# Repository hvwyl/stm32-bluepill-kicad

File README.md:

# stm32-bluepill-kicad
STM32 BluePill redesigned by KiCad

## Schematic

## PCB Layout

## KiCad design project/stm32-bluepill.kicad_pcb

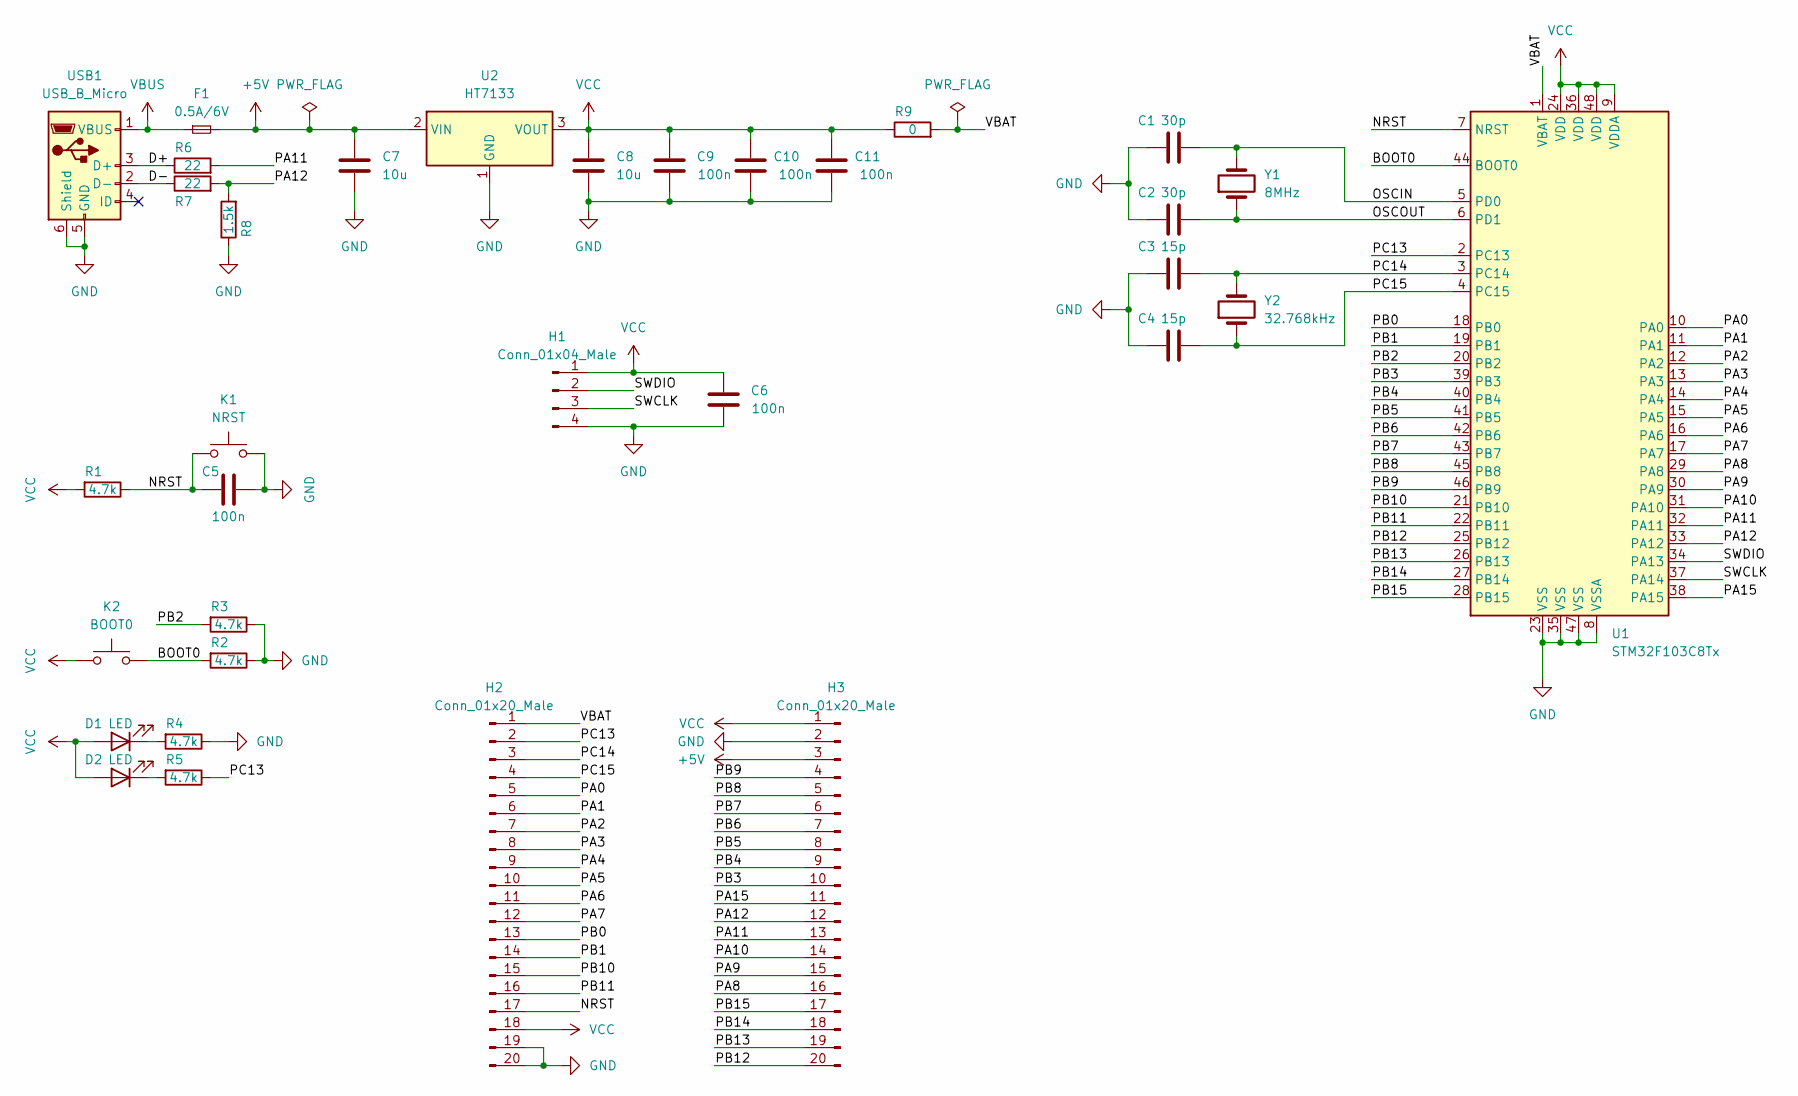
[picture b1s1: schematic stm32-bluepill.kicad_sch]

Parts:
C1, C2: 30p; C_0603_1608Metric
C3, C4: 15p; C_0603_1608Metric
C5, C6, C9, C10, C11: 100n; C_0603_1608Metric
C7, C8: 10u; C_0805_2012Metric
D1, D2: LED; LED_0805_2012Metric
F1: 0.5A/6V; Fuse_0805_2012Metric
H1: Conn_01x04_Male; PinHeader_1x04_P2.54mm_Vertical
H2, H3: Conn_01x20_Male; PinHeader_1x20_P2.54mm_Vertical
K1: NRST; SW_SPST_CK_RS282G05A3
K2: BOOT0; SW_SPST_CK_RS282G05A3
R1, R2, R3, R4, R5: 4.7k; R_0603_1608Metric
R6, R7: 22; R_0603_1608Metric
R8: 1.5k; R_0603_1608Metric
R9: 0; R_0603_1608Metric
U1: STM32F103C8Tx; LQFP-48_7x7mm_P0.5mm
U2: HT7133; SOT-89-3
USB1: USB_B_Micro; USB_Micro-B_Amphenol_10118194_Horizontal
Y1: 8MHz; Crystal_HC49-4H_Vertical
Y2: 32.768kHz; Crystal_DS26_D2.0mm_L6.0mm_Horizontal

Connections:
+5V: C7.1, F1.2, H3.3, U2.2 (VIN)
/BOOT0: K2.2, R2.2, U1.44 (BOOT0)
/D+: R6.1, USB1.3 (D+)
/D-: R7.1, USB1.2 (D-)
/NRST: C5.2, H2.17, K1.1, R1.1, U1.7 (NRST)
/OSCIN: C1.2, U1.5 (PD0), Y1.2
/OSCOUT: C2.2, U1.6 (PD1), Y1.1
/PA0: H2.5, U1.10 (PA0)
/PA1: H2.6, U1.11 (PA1)
/PA2: H2.7, U1.12 (PA2)
/PA3: H2.8, U1.13 (PA3)
/PA4: H2.9, U1.14 (PA4)
/PA5: H2.10, U1.15 (PA5)
/PA6: H2.11, U1.16 (PA6)
/PA7: H2.12, U1.17 (PA7)
/PA8: H3.16, U1.29 (PA8)
/PA9: H3.15, U1.30 (PA9)
/PA10: H3.14, U1.31 (PA10)
/PA11: H3.13, R6.2, U1.32 (PA11)
/PA12: H3.12, R7.2, R8.2, U1.33 (PA12)
/PA15: H3.11, U1.38 (PA15)
/PB0: H2.13, U1.18 (PB0)
/PB1: H2.14, U1.19 (PB1)
/PB2: R3.2, U1.20 (PB2)
/PB3: H3.10, U1.39 (PB3)
/PB4: H3.9, U1.40 (PB4)
/PB5: H3.8, U1.41 (PB5)
/PB6: H3.7, U1.42 (PB6)
/PB7: H3.6, U1.43 (PB7)
/PB8: H3.5, U1.45 (PB8)
/PB9: H3.4, U1.46 (PB9)
/PB10: H2.15, U1.21 (PB10)
/PB11: H2.16, U1.22 (PB11)
/PB12: H3.20, U1.25 (PB12)
/PB13: H3.19, U1.26 (PB13)
/PB14: H3.18, U1.27 (PB14)
/PB15: H3.17, U1.28 (PB15)
/PC13: H2.2, R5.1, U1.2 (PC13)
/PC14: C3.2, H2.3, U1.3 (PC14), Y2.2
/PC15: C4.2, H2.4, U1.4 (PC15), Y2.1
/SWCLK: H1.3, U1.37 (PA14)
/SWDIO: H1.2, U1.34 (PA13)
/VBAT: H2.1, R9.2, U1.1 (VBAT)
GND: C1.1, C2.1, C3.1, C4.1, C5.1, C6.1, C7.2, C8.2, C9.1, C10.1, C11.1, H1.4, H2.19, H2.20, H3.2, K1.2, R2.1, R3.1, R4.1, R8.1, U1.8 (VSSA), U1.23 (VSS), U1.35 (VSS), U1.47 (VSS), U2.1 (GND), USB1.5 (GND), USB1.6 (Shield)
unnamed: D1.1 (K), R4.2
unnamed: D2.1 (K), R5.2
VBUS: F1.1, USB1.1 (VBUS)
VCC: C6.2, C8.1, C9.2, C10.2, C11.2, D1.2 (A), D2.2 (A), H1.1, H2.18, H3.1, K2.1, R1.2, R9.1, U1.9 (VDDA), U1.24 (VDD), U1.36 (VDD), U1.48 (VDD), U2.3 (VOUT)

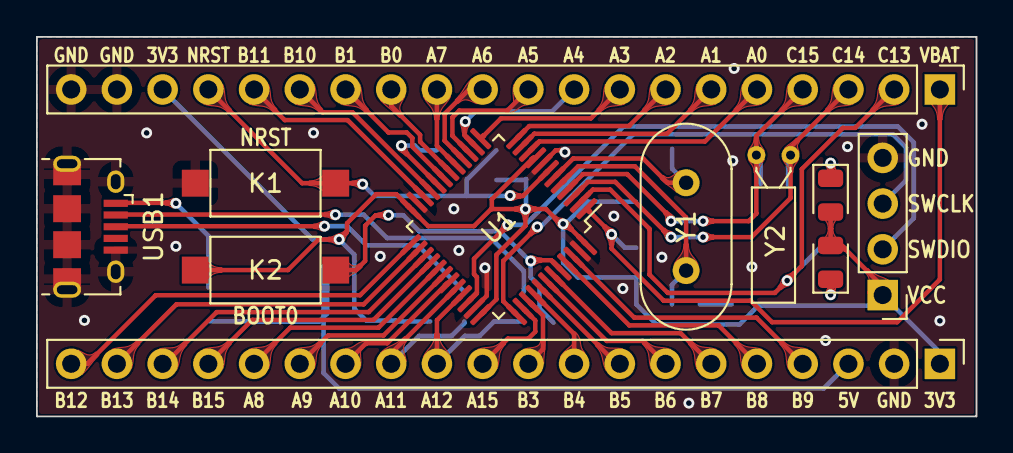
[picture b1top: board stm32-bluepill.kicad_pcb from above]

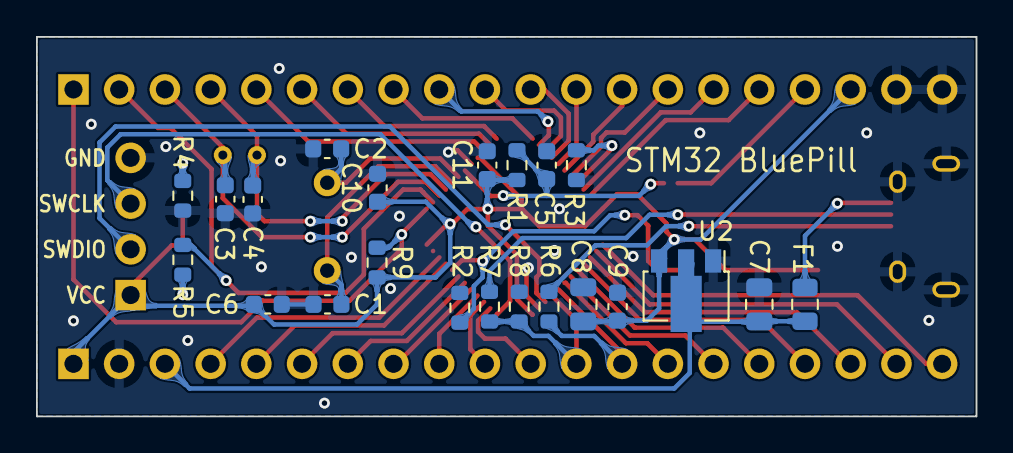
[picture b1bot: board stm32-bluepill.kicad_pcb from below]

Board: 2 copper layers, 52.2 x 21.1 mm, 33 parts (22 on the bottom side), 48 nets.

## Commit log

2023-08-09 version 1.0.0
